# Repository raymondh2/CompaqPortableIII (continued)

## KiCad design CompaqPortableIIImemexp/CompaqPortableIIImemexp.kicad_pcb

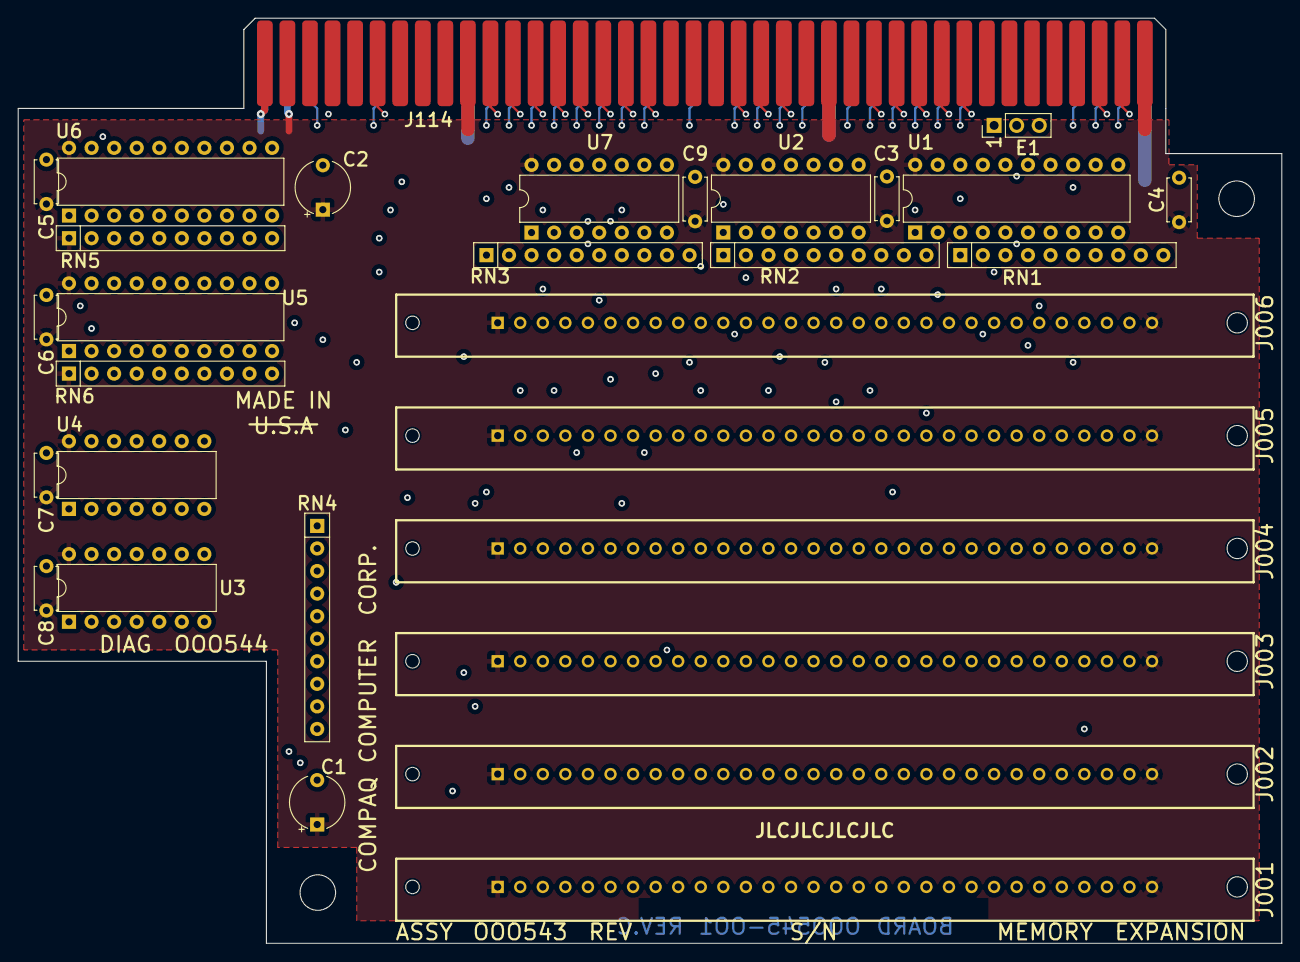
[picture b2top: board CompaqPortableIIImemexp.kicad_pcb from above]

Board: 4 copper layers, 142.2 x 104.1 mm, 32 parts (0 on the bottom side), 104 nets.

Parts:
C1, C2: 10u; CP_Radial_Tantal_D6.0mm_P5.00mm
C3, C4, C5, C6, C7, C8, C9: 47n; C_Disc_D4.7mm_W2.5mm_P5.00mm
E1: Conn_01x03; PinHeader_1x03_P2.54mm_Vertical
H1, H2: MountingHole_Pad; MountingHole_4mm
J001, J002, J003, J004, J005, J006: Conn_SIMM30
J114: Conn_02x40_Counter_Clockwise; Conn_Edge_PCB_02x40_mirror_memexp
RN1, RN2, RN3, RN4: 33; R_Array_SIP10
RN5, RN6: 8.2k; R_Array_SIP10
U1: 74F244; DIP-20_W7.62mm
U2, U4: 74F32; DIP-14_W7.62mm
U3: 74F00; DIP-14_W7.62mm
U5, U6: 74F245; DIP-20_W7.62mm
U7: 74F10; DIP-14_W7.62mm

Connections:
+5V: C1.1, C2.1, C3.1, C4.1, C5.1, C6.1, C7.1, C8.1, C9.1, J001.1 (VCC), J001.30 (VCC), J002.1 (VCC), J002.30 (VCC), J003.1 (VCC), J003.30 (VCC), J004.1 (VCC), J004.30 (VCC), J005.1 (VCC), J005.30 (VCC), J006.1 (VCC), J006.30 (VCC), J114.39, J114.41, J114.55, J114.71, RN5.1 (common), RN6.1 (common), U1.20 (VCC), U2.14 (VCC), U3.14 (VCC), U4.14 (VCC), U5.20 (VCC), U6.20 (VCC), U7.14 (VCC)
/1u3-16j114: J114.16, U3.1
/2u7-58j114: J114.58, U7.2, U7.3, U7.10
/8u4-19u6: U4.8, U6.19 (CE)
/11u4-19u5: U4.11, U5.19 (CE)
/12u4-21j114: J114.21, U4.10, U4.12
/13u3-17j114: J114.17, U3.13
/17u1-2E1: E1.2, U1.15 (I2b)
/A2: E1.3, J114.38
/A10: J114.9, U2.9, U2.12
/CAS: J114.35, U3.2, U3.12
/CASEVEN: J002.2 (~CAS), J002.28 (~CASP), J004.2 (~CAS), J004.28 (~CASP), J006.2 (~CAS), J006.28 (~CASP), RN4.2 (R1.2)
/CASODD: J001.2 (~CAS), J001.28 (~CASP), J003.2 (~CAS), J003.28 (~CASP), J005.2 (~CAS), J005.28 (~CASP), RN4.4 (R2.2)
/MA0: J114.10, U1.17 (I3b)
/MA1: E1.1, J114.50
/MA2: J114.11, U1.13 (I1b)
/MA3: J114.51, U1.11 (I0b)
/MA4: J114.12, U1.8 (I3a)
/MA5: J114.52, U1.6 (I2a)
/MA6: J114.13, U1.4 (I1a)
/MA7: J114.53, U1.2 (I0a)
/MA8: J114.14, U2.1, U2.4
/MEM-A0: J001.4 (A0), J002.4 (A0), J003.4 (A0), J004.4 (A0), J005.4 (A0), J006.4 (A0), RN2.6 (R3.2)
/MEM-A1: J001.5 (A1), J002.5 (A1), J003.5 (A1), J004.5 (A1), J005.5 (A1), J006.5 (A1), RN2.4 (R2.2)
/MEM-A2: J001.7 (A2), J002.7 (A2), J003.7 (A2), J004.7 (A2), J005.7 (A2), J006.7 (A2), RN2.2 (R1.2)
/MEM-A3: J001.8 (A3), J002.8 (A3), J003.8 (A3), J004.8 (A3), J005.8 (A3), J006.8 (A3), RN1.10 (R5.2)
/MEM-A4: J001.11 (A4), J002.11 (A4), J003.11 (A4), J004.11 (A4), J005.11 (A4), J006.11 (A4), RN1.8 (R4.2)
/MEM-A5: J001.12 (A5), J002.12 (A5), J003.12 (A5), J004.12 (A5), J005.12 (A5), J006.12 (A5), RN1.6 (R3.2)
/MEM-A6: J001.14 (A6), J002.14 (A6), J003.14 (A6), J004.14 (A6), J005.14 (A6), J006.14 (A6), RN1.4 (R2.2)
/MEM-A7: J001.15 (A7), J002.15 (A7), J003.15 (A7), J004.15 (A7), J005.15 (A7), J006.15 (A7), RN1.2 (R1.2)
/MEMEVEN-A8: J002.17 (A8), J004.17 (A8), J006.17 (A8), RN2.10 (R5.2)
/MEMEVEN-A9: J002.18 (A9), J004.18 (A9), J006.18 (A9), RN3.4 (R2.2)
/MEMEVEN-DP: J002.29 (DP), J004.29 (DP), J006.29 (DP), J114.42
/MEMEVEN-QP: J002.26 (QP), J004.26 (QP), J006.26 (QP), J114.43
/MEMODD-A8: J001.17 (A8), J003.17 (A8), J005.17 (A8), RN2.8 (R4.2)
/MEMODD-A9: J001.18 (A9), J003.18 (A9), J005.18 (A9), RN3.2 (R1.2)
/MEMODD-DP: J001.29 (DP), J003.29 (DP), J005.29 (DP), J114.2
/MEMODD-QP: J001.26 (QP), J003.26 (QP), J005.26 (QP), J114.3
/MEM_WEDIR: RN3.10 (R5.2), U5.1 (A->B), U6.1 (A->B)
/Memory/MD0: J001.3 (DQ0), J003.3 (DQ0), J005.3 (DQ0), RN6.7 (R6), U5.14 (B4)
/Memory/MD1: J001.6 (DQ1), J003.6 (DQ1), J005.6 (DQ1), RN6.9 (R8), U5.12 (B6)
/Memory/MD2: J001.10 (DQ2), J003.10 (DQ2), J005.10 (DQ2), RN6.8 (R7), U5.13 (B5)
/Memory/MD3: J001.13 (DQ3), J003.13 (DQ3), J005.13 (DQ3), RN6.10 (R9), U5.11 (B7)
/Memory/MD4: J001.16 (DQ4), J003.16 (DQ4), J005.16 (DQ4), RN6.5 (R4), U5.16 (B2)
/Memory/MD5: J001.20 (DQ5), J003.20 (DQ5), J005.20 (DQ5), RN6.4 (R3), U5.17 (B1)
/Memory/MD6: J001.23 (DQ6), J003.23 (DQ6), J005.23 (DQ6), RN6.3 (R2), U5.18 (B0)
/Memory/MD7: J001.25 (DQ7), J003.25 (DQ7), J005.25 (DQ7), RN6.6 (R5), U5.15 (B3)
/Memory/MD8: J002.3 (DQ0), J004.3 (DQ0), J006.3 (DQ0), RN5.7 (R6), U6.14 (B4)
/Memory/MD9: J002.6 (DQ1), J004.6 (DQ1), J006.6 (DQ1), RN5.9 (R8), U6.12 (B6)
/Memory/MD10: J002.10 (DQ2), J004.10 (DQ2), J006.10 (DQ2), RN5.8 (R7), U6.13 (B5)
/Memory/MD11: J002.13 (DQ3), J004.13 (DQ3), J006.13 (DQ3), RN5.6 (R5), U6.15 (B3)
/Memory/MD12: J002.16 (DQ4), J004.16 (DQ4), J006.16 (DQ4), RN5.4 (R3), U6.17 (B1)
/Memory/MD13: J002.20 (DQ5), J004.20 (DQ5), J006.20 (DQ5), RN5.5 (R4), U6.16 (B2)
/Memory/MD14: J002.23 (DQ6), J004.23 (DQ6), J006.23 (DQ6), RN5.10 (R9), U6.11 (B7)
/Memory/MD15: J002.25 (DQ7), J004.25 (DQ7), J006.25 (DQ7), RN5.3 (R2), U6.18 (B0)
/RAM 2 RAS: J114.57, U7.5
/RAM 3 RAS: J114.19, U7.9
/RAM 4 RAS: J114.59, U7.1
/RAS: J114.18, U3.4, U7.4, U7.11, U7.13
/RAS1: J001.27 (~RAS), J002.27 (~RAS), RN4.10 (R5.2)
/RAS2: J003.27 (~RAS), J004.27 (~RAS), RN4.8 (R4.2)
/RAS3: J005.27 (~RAS), J006.27 (~RAS), RN4.6 (R3.2)
/SA0: J114.49, U4.13
/SBHE: J114.75, U4.9
/SD0: J114.23, U5.6 (A4)
/SD1: J114.63, U5.8 (A6)
/SD2: J114.24, U5.7 (A5)
/SD3: J114.64, U5.9 (A7)
/SD4: J114.25, U5.4 (A2)
/SD5: J114.65, U5.3 (A1)
/SD6: J114.26, U5.2 (A0)
/SD7: J114.66, U5.5 (A3)
/SD8: J114.27, U6.6 (A4)
/SD9: J114.67, U6.8 (A6)
/SD10: J114.28, U6.7 (A5)
/SD11: J114.68, U6.5 (A3)
/SD12: J114.29, U6.3 (A1)
/SD13: J114.69, U6.4 (A2)
/SD14: J114.30, U6.9 (A7)
/SD15: J114.70, U6.2 (A0)
/WEEVEN: J002.21 (~WE), J004.21 (~WE), J006.21 (~WE), RN3.6 (R3.2)
/WEODD: J001.21 (~WE), J003.21 (~WE), J005.21 (~WE), RN3.8 (R4.2)
/~MEMW: J114.4, U3.5, U4.2, U4.5
GND: C1.2, C2.2, C3.2, C4.2, C5.2, C6.2, C7.2, C8.2, C9.2, J001.9 (GND), J001.22 (GND), J002.9 (GND), J002.22 (GND), J003.9 (GND), J003.22 (GND), J004.9 (GND), J004.22 (GND), J005.9 (GND), J005.22 (GND), J006.9 (GND), J006.22 (GND), J114.1, J114.15, J114.31, J114.40, J114.80, U1.1 (OEa), U1.10 (GND), U1.19 (OEb), U2.2, U2.5, U2.7 (GND), U2.10, U2.13, U3.7 (GND), U4.1, U4.4, U4.7 (GND), U5.10 (GND), U6.10 (GND), U7.7 (GND)
unnamed: RN1.1 (R1.1), U1.18 (O0a)
unnamed: RN1.3 (R2.1), U1.16 (O1a)
unnamed: RN1.5 (R3.1), U1.14 (O2a)
unnamed: RN1.7 (R4.1), U1.12 (O3a)
unnamed: RN1.9 (R5.1), U1.9 (O0b)
unnamed: RN2.1 (R1.1), U1.7 (O1b)
unnamed: RN2.3 (R2.1), U1.5 (O2b)
unnamed: RN2.5 (R3.1), U1.3 (O3b)
unnamed: RN2.7 (R4.1), U2.3
unnamed: RN2.9 (R5.1), U2.6
unnamed: RN3.1 (R1.1), U2.8
unnamed: RN3.3 (R2.1), U2.11
unnamed: RN3.5 (R3.1), U4.3
unnamed: RN3.7 (R4.1), U4.6
unnamed: RN3.9 (R5.1), U3.6
unnamed: RN4.1 (R1.1), U3.11
unnamed: RN4.3 (R2.1), U3.3
unnamed: RN4.5 (R3.1), U7.12
unnamed: RN4.7 (R4.1), U7.8
unnamed: RN4.9 (R5.1), U7.6

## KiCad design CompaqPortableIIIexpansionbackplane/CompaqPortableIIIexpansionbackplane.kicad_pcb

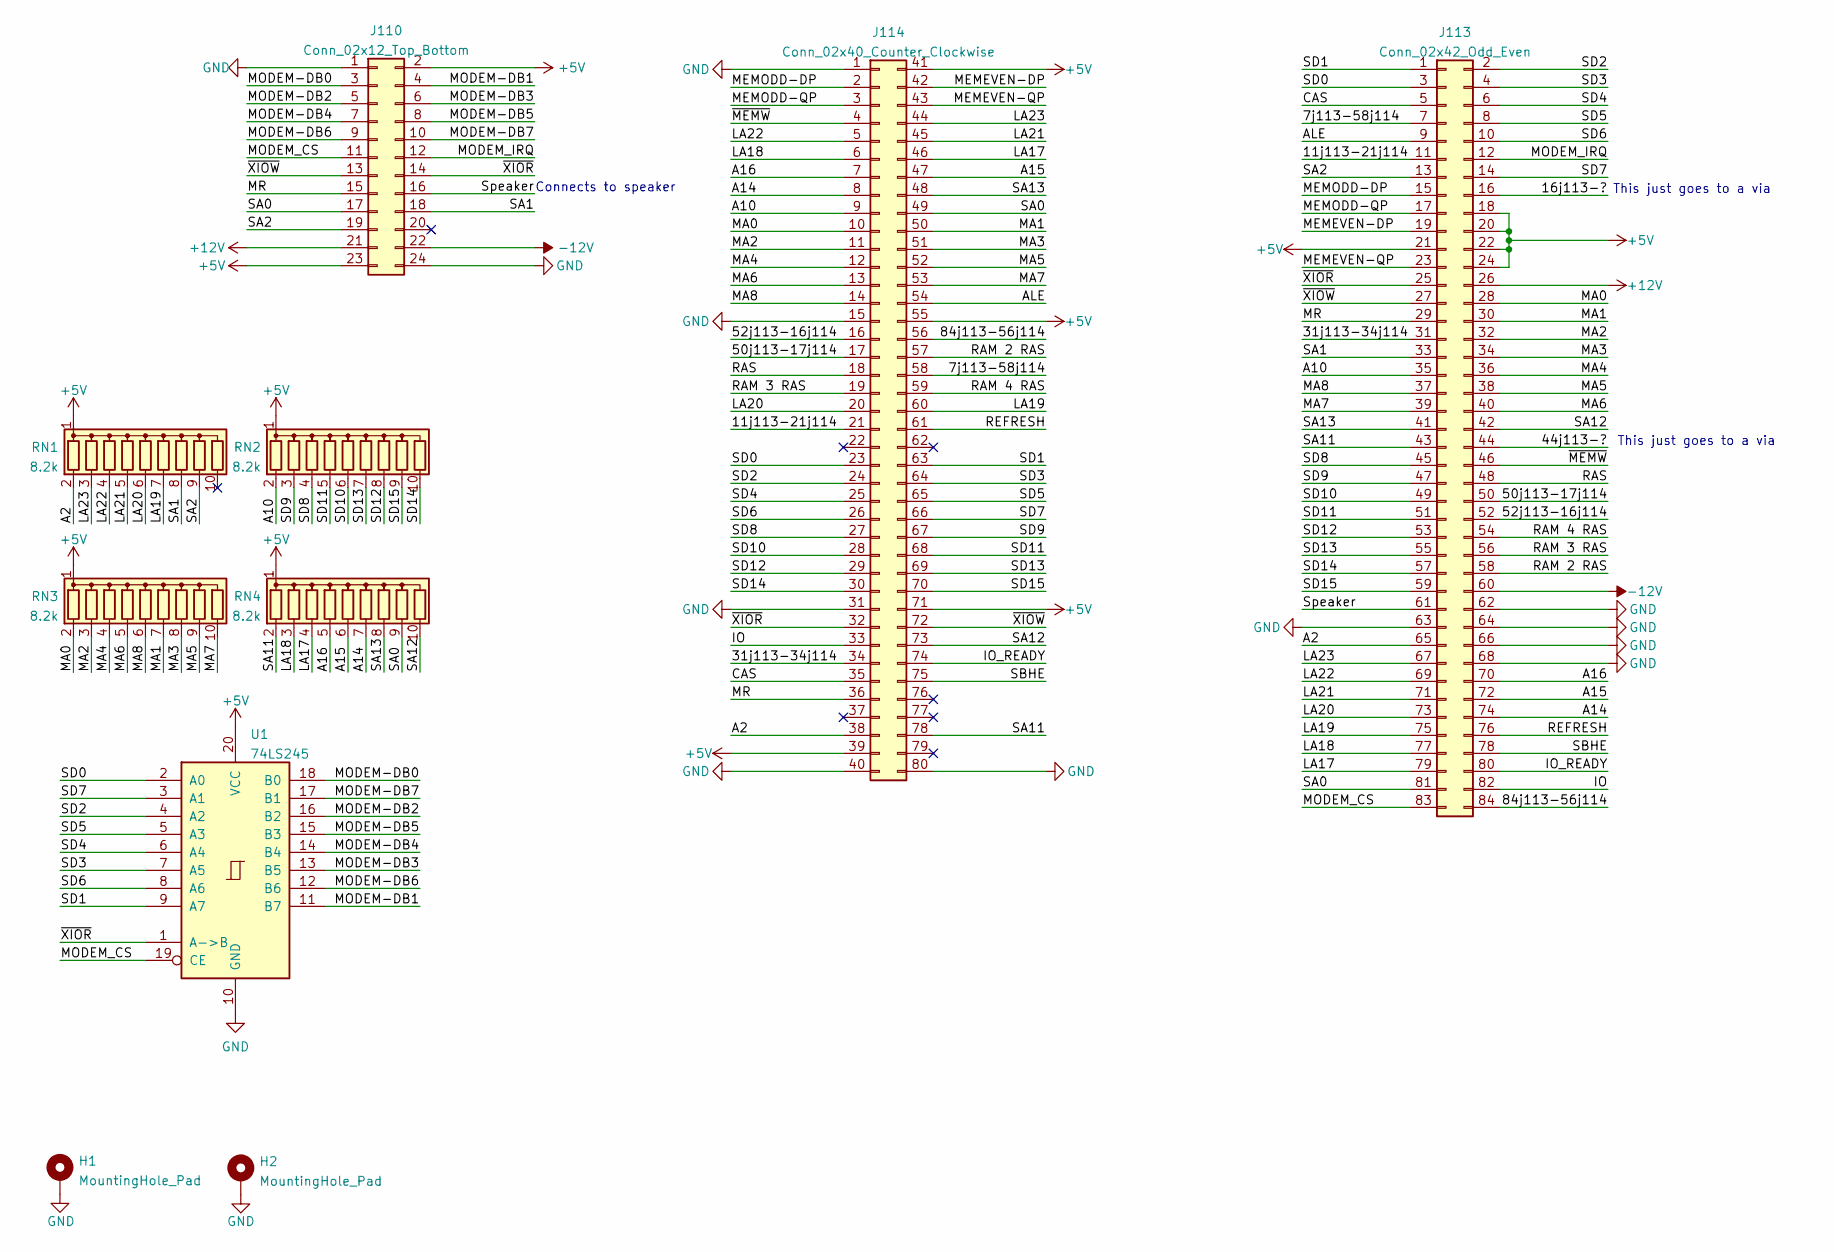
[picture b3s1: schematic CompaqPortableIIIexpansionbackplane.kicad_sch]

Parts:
H1, H2: MountingHole_Pad; MountingHole_4mm_Pad_TopOnly
J110: Conn_02x12_Top_Bottom; 5530843-1_oddeven; PartNumber 5530843-1
J113: Conn_02x42_Odd_Even; PinSocket_2x42_P1.27mm_Vertical_2.54row; PartNumber 6-104068-7
J114: Conn_02x40_Counter_Clockwise; 2-5530843-0_mirror; PartNumber 2-5530843-0
RN1, RN2, RN3, RN4: 8.2k; R_Array_SIP10; PartNumber 4610X-101-822LF
U1: 74LS245; DIP-20_W7.62mm; PartNumber 74LS245N

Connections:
+5V: J110.2, J110.23, J113.18, J113.20, J113.21, J113.22, J113.24, J114.39, J114.41, J114.55, J114.71, RN1.1 (common), RN2.1 (common), RN3.1 (common), RN4.1 (common), U1.20 (VCC)
+12V: J110.21, J113.26
-12V: J110.22, J113.60
/7j113-58j114: J113.7, J114.58
/11j113-21j114: J113.11, J114.21
/16j113-?: J113.16
/31j113-34j114: J113.31, J114.34
/44j113-?: J113.44
/50j113-17j114: J113.50, J114.17
/52j113-16j114: J113.52, J114.16
/54j113-59j114: J113.54, J114.59
/56j113-19j114: J113.56, J114.19
/84j113-56j114: J113.84, J114.56
/A2: J113.65, J114.38, RN1.2 (R1)
/A10: J113.35, J114.9, RN2.2 (R1)
/A14: J113.74, J114.8, RN4.7 (R6)
/A15: J113.72, J114.47, RN4.6 (R5)
/A16: J113.70, J114.7, RN4.5 (R4)
/ALE: J113.9, J114.54
/BA00: J110.17, J113.81, J114.49, RN4.9 (R8)
/BA01: J110.18, J113.33, RN1.8 (R7)
/BA02: J110.19, J113.13, RN1.9 (R8)
/BA11: J113.43, J114.78, RN4.2 (R1)
/BA12: J113.42, J114.73, RN4.10 (R9)
/BA13: J113.41, J114.48, RN4.8 (R7)
/CAS: J113.5, J114.35
/IO: J113.82, J114.33
/IOR: J110.14, J113.25, J114.32, U1.1 (A->B)
/IOW: J110.13, J113.27, J114.72
/IO_READY: J113.80, J114.74
/LA17: J113.79, J114.46, RN4.4 (R3)
/LA18: J113.77, J114.6, RN4.3 (R2)
/LA19: J113.75, J114.60, RN1.7 (R6)
/LA20: J113.73, J114.20, RN1.6 (R5)
/LA21: J113.71, J114.45, RN1.5 (R4)
/LA22: J113.69, J114.5, RN1.4 (R3)
/LA23: J113.67, J114.44, RN1.3 (R2)
/MA0: J113.28, J114.10, RN3.2 (R1)
/MA1: J113.30, J114.50, RN3.7 (R6)
/MA2: J113.32, J114.11, RN3.3 (R2)
/MA3: J113.34, J114.51, RN3.8 (R7)
/MA4: J113.36, J114.12, RN3.4 (R3)
/MA5: J113.38, J114.52, RN3.9 (R8)
/MA6: J113.40, J114.13, RN3.5 (R4)
/MA7: J113.39, J114.53, RN3.10 (R9)
/MA8: J113.37, J114.14, RN3.6 (R5)
/MEMEVEN-DP: J113.19, J114.42
/MEMEVEN-QP: J113.23, J114.43
/MEMODD-DP: J113.15, J114.2
/MEMODD-QP: J113.17, J114.3
/MODEM-DB0: J110.3, U1.18 (B0)
/MODEM-DB1: J110.4, U1.11 (B7)
/MODEM-DB2: J110.5, U1.16 (B2)
/MODEM-DB3: J110.6, U1.13 (B5)
/MODEM-DB4: J110.7, U1.14 (B4)
/MODEM-DB5: J110.8, U1.15 (B3)
/MODEM-DB6: J110.9, U1.12 (B6)
/MODEM-DB7: J110.10, U1.17 (B1)
/MODEM_CS: J110.11, J113.83, U1.19 (CE)
/MODEM_IRQ: J110.12, J113.12
/MR: J110.15, J113.29, J114.36
/RAS: J113.48, J114.18
/REFRESH: J113.76, J114.61
/SBHE: J113.78, J114.75
/SD0: J113.3, J114.23, U1.2 (A0)
/SD1: J113.1, J114.63, U1.9 (A7)
/SD2: J113.2, J114.24, U1.4 (A2)
/SD3: J113.4, J114.64, U1.7 (A5)
/SD4: J113.6, J114.25, U1.6 (A4)
/SD5: J113.8, J114.65, U1.5 (A3)
/SD6: J113.10, J114.26, U1.8 (A6)
/SD7: J113.14, J114.66, U1.3 (A1)
/SD8: J113.45, J114.27, RN2.4 (R3)
/SD9: J113.47, J114.67, RN2.3 (R2)
/SD10: J113.49, J114.28, RN2.6 (R5)
/SD11: J113.51, J114.68, RN2.5 (R4)
/SD12: J113.53, J114.29, RN2.8 (R7)
/SD13: J113.55, J114.69, RN2.7 (R6)
/SD14: J113.57, J114.30, RN2.10 (R9)
/SD15: J113.59, J114.70, RN2.9 (R8)
/Speaker: J110.16, J113.61
/~MEMW: J113.46, J114.4
/~RAS2: J113.58, J114.57
GND: H1.1, H2.1, J110.1, J110.24, J113.62, J113.63, J113.64, J113.66, J113.68, J114.1, J114.15, J114.31, J114.40, J114.80, U1.10 (GND)

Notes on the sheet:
Connects to speaker
This just goes to a via

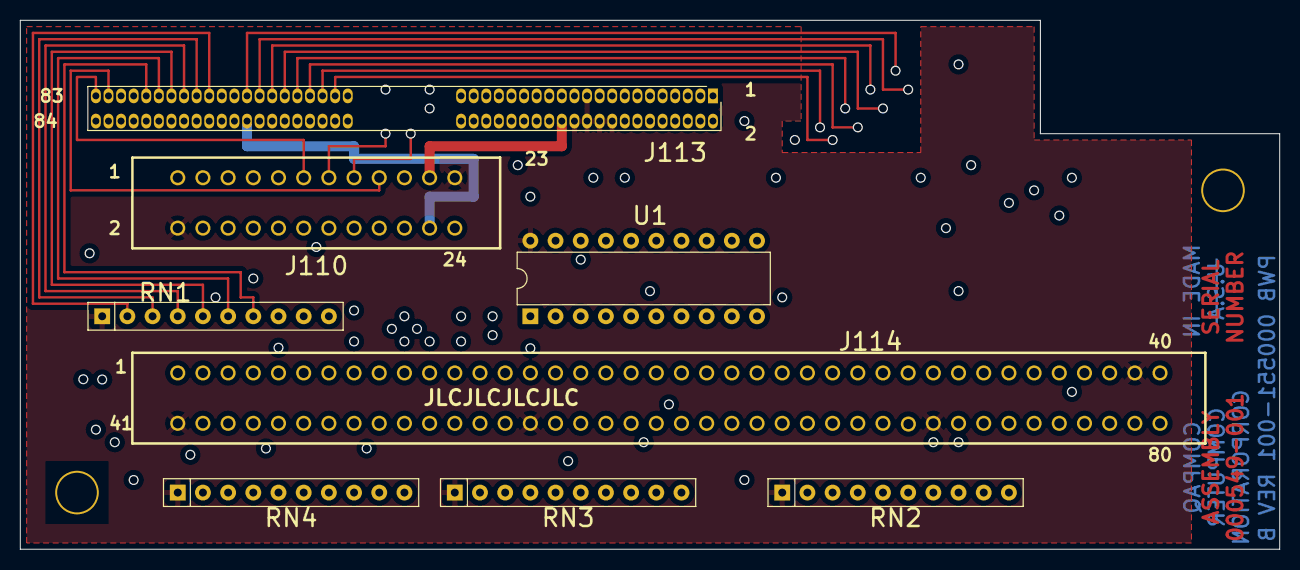
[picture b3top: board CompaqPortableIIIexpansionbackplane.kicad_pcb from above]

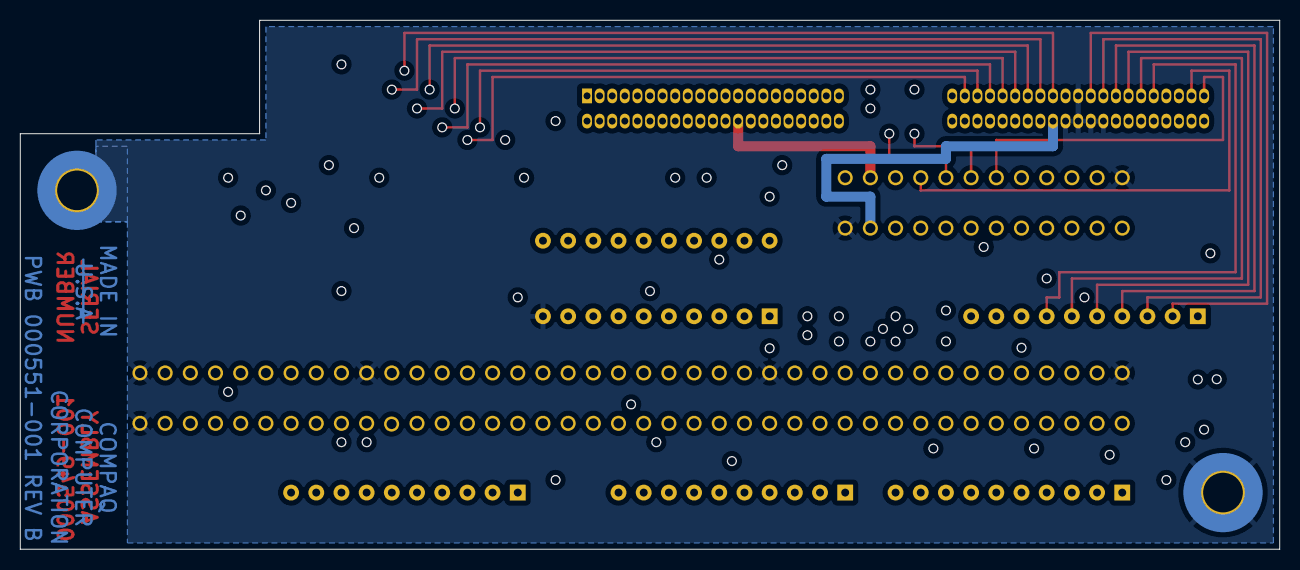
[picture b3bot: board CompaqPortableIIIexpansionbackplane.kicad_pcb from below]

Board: 4 copper layers, 127.0 x 53.3 mm, 10 parts (2 on the bottom side), 82 nets.

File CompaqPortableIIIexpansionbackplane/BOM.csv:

"Reference","Value","PartNumber","Qty"
"J110","Conn_02x12_Top_Bottom","5530843-1","1"
"J113","Conn_02x42_Odd_Even","6-104068-7","1"
"J114","Conn_02x40_Counter_Clockwise","2-5530843-0","1"
"RN1,RN2,RN3,RN4","8.2k","4610X-101-822LF","4"
"U1","74LS245","SN74LS245N","1"

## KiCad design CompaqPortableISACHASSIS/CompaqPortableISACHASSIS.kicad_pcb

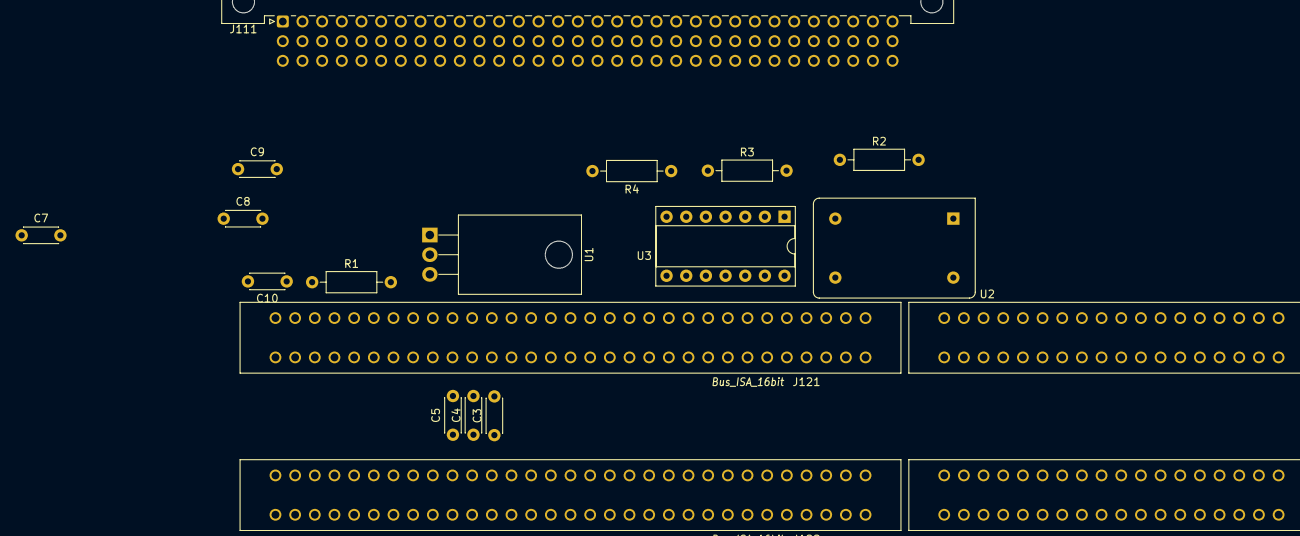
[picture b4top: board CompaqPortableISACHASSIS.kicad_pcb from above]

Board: 2 copper layers, 17 parts (0 on the bottom side), 102 nets, no tracks yet.

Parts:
C3, C7, C10: 10n; C_Disc_D4.3mm_W1.9mm_P5.00mm
C4, C5, C8, C9: 100n; C_Disc_D4.3mm_W1.9mm_P5.00mm
J111: DIN41612_96abc; DIN41612_R_3x32_Male_Horizontal_THT
J121, J122: Bus_ISA_16bit; Conn_Edge_ISA16
R1: 1k; R_Axial_DIN0207_L6.3mm_D2.5mm_P10.16mm_Horizontal
R2, R4: 30?; R_Axial_DIN0207_L6.3mm_D2.5mm_P10.16mm_Horizontal
R3: 150; R_Axial_DIN0207_L6.3mm_D2.5mm_P10.16mm_Horizontal
U1: L7905; TO-220-3_Horizontal_TabDown
U2: CXO_DIP14; Oscillator_DIP-14
U3: 74LS125; DIP-14_W7.62mm_Socket

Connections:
+5V: J121.3 (+5V), J121.29 (VCC), J121.78 (+5V), J122.3 (+5V), J122.29 (VCC), J122.78 (+5V), U2.1 (EN), U2.14 (Vcc), U3.14 (VCC)
+12V: J111.a6 (Pin_c6), J111.a20 (Pin_c20), J121.9 (+12V), J122.9 (+12V)
-5V: J121.5 (-5V), J122.5 (-5V)
-12V: J111.b5 (Pin_c5), J121.7 (-12V), J122.7 (-12V), U1.2 (VI)
/5v_unfused: J111.a2 (Pin_c2), J111.a8 (Pin_c8), J111.c20
/AEN: J111.a7 (Pin_c7), J121.42 (AEN), J122.42 (AEN)
/ALE: J111.b19 (Pin_c19), J121.28 (ALE), J122.28 (ALE)
/BA00: J111.c21, J121.62 (BA00), J122.62 (BA00)
/BA01: J111.b20 (Pin_c20), J121.61 (BA01), J122.61 (BA01)
/BA02: J111.a19 (Pin_c19), J121.60 (BA02), J122.60 (BA02)
/BA03: J111.c19, J121.59 (BA03), J122.59 (BA03)
/BA04: J111.b18 (Pin_c18), J121.58 (BA04), J122.58 (BA04)
/BA05: J111.a17 (Pin_c17), J121.57 (BA05), J122.57 (BA05)
/BA06: J111.c17, J121.56 (BA06), J122.56 (BA06)
/BA07: J111.b16 (Pin_c16), J121.55 (BA07), J122.55 (BA07)
/BA08: J111.a15 (Pin_c15), J121.54 (BA08), J122.54 (BA08)
/BA09: J111.c15, J121.53 (BA09), J122.53 (BA09)
/BA10: J111.b14 (Pin_c14), J121.52 (BA10), J122.52 (BA10)
/BA11: J111.a13 (Pin_c13), J121.51 (BA11), J122.51 (BA11)
/BA12: J111.c13, J121.50 (BA12), J122.50 (BA12)
/BA13: J111.b12 (Pin_c12), J121.49 (BA13), J122.49 (BA13)
/BA14: J111.a11 (Pin_c11), J121.48 (BA14), J122.48 (BA14)
/BA15: J111.c11, J121.47 (BA15), J122.47 (BA15)
/BA16: J111.b10 (Pin_c10), J121.46 (BA16), J122.46 (BA16)
/BA17: J111.a9 (Pin_c9), J121.45 (BA17), J122.45 (BA17)
/BA18: J111.c9, J121.44 (BA18), J122.44 (BA18)
/BA19: J111.b8 (Pin_c8), J121.43 (BA19), J122.43 (BA19)
/CLK: J121.20 (CLK), J122.20 (CLK), R4.2
/D8: J111.b28 (Pin_c28), J121.91 (D8), J122.91 (D8)
/D9: J111.c29, J121.92 (D9), J122.92 (D9)
/D10: J111.a29 (Pin_c29), J121.93 (D10), J122.93 (D10)
/D11: J111.b30 (Pin_c30), J121.94 (D11), J122.94 (D11)
/D12: J111.c31, J121.95 (D12), J122.95 (D12)
/D13: J111.a31 (Pin_c31), J121.96 (D13), J122.96 (D13)
/D14: J111.c32, J121.97 (D14), J122.97 (D14)
/D15: J111.a32 (Pin_c32), J121.98 (D15), J122.98 (D15)
/DB0: J111.b6 (Pin_c6), J121.40 (DB0), J122.40 (DB0)
/DB1: J111.a5 (Pin_c5), J121.39 (DB1), J122.39 (DB1)
/DB2: J111.c5, J121.38 (DB2), J122.38 (DB2)
/DB3: J111.b4 (Pin_c4), J121.37 (DB3), J122.37 (DB3)
/DB4: J111.a3 (Pin_c3), J121.36 (DB4), J122.36 (DB4)
/DB5: J111.c3, J121.35 (DB5), J122.35 (DB5)
/DB6: J111.b2 (Pin_c2), J121.34 (DB6), J122.34 (DB6)
/DB7: J111.a1 (Pin_c1), J121.33 (DB7), J122.33 (DB7)
/DRQ0: J111.b27 (Pin_c27), J121.71 (DRQ0), J122.71 (DRQ0)
/DRQ1: J111.a12 (Pin_c12), J121.18 (DRQ1), J122.18 (DRQ1)
/DRQ2: J111.a4 (Pin_c4), J121.6 (DRQ2), J122.6 (DRQ2)
/DRQ3: J111.b11 (Pin_c11), J121.16 (DRQ3), J122.16 (DRQ3)
/DRQ5: J111.a28 (Pin_c28), J121.73 (DRQ5), J122.73 (DRQ5)
/DRQ6: J111.c30, J121.75 (DRQ6), J122.75 (DRQ6)
/DRQ7: J111.b31 (Pin_c31), J121.77 (DRQ7), J122.77 (DRQ7)
/IO: J111.c1, J121.32 (IO), J122.32 (IO)
/IO_READY: J111.c7, J121.41 (IO_READY), J122.41 (IO_READY)
/IRQ2: J111.b3 (Pin_c3), J121.4 (IRQ2), J122.4 (IRQ2)
/IRQ3: J111.b17 (Pin_c17), J121.25 (IRQ3), J122.25 (IRQ3)
/IRQ4: J111.a16 (Pin_c16), J121.24 (IRQ4), J122.24 (IRQ4)
/IRQ5: J111.c16, J121.23 (IRQ5), J122.23 (IRQ5)
/IRQ6: J111.b15 (Pin_c15), J121.22 (IRQ6), J122.22 (IRQ6)
/IRQ7: J111.a14 (Pin_c14), J121.21 (IRQ7), J122.21 (IRQ7)
/IRQ10: J111.b23 (Pin_c23), J121.65 (IRQ10), J122.65 (IRQ10)
/IRQ11: J111.c24, J121.66 (IRQ11), J122.66 (IRQ11)
/IRQ12: J111.a24 (Pin_c24), J121.67 (IRQ12), J122.67 (IRQ12)
/IRQ14: J111.c26, J121.69 (IRQ14), J122.69 (IRQ14)
/IRQ15: J111.b25 (Pin_c25), J121.68 (IRQ15), J122.68 (IRQ15)
/LA17: J111.b26 (Pin_c26), J121.88 (LA17), J122.88 (LA17)
/LA18: J111.a25 (Pin_c25), J121.87 (LA18), J122.87 (LA18)
/LA19: J111.c25, J121.86 (LA19), J122.86 (LA19)
/LA20: J111.b24 (Pin_c24), J121.85 (LA20), J122.85 (LA20)
/LA21: J111.a23 (Pin_c23), J121.84 (LA21), J122.84 (LA21)
/LA22: J111.c23, J121.83 (LA22), J122.83 (LA22)
/LA23: J111.b22 (Pin_c22), J121.82 (LA23), J122.82 (LA23)
/MASTER: J111.b32 (Pin_c32), J121.79 (MASTER), J122.79 (MASTER)
/OSC: J121.30 (OSC), J122.30 (OSC), R2.2
/OWS_N: J111.c6, J121.8 (UNUSED), J122.8 (UNUSED)
/RESET: C10.1, J111.c2, J121.2 (RESET), J122.2 (RESET)
/SBHE: J111.a21 (Pin_c21), J121.81 (SBHE), J122.81 (SBHE)
/SYSCLK: J111.c14, U3.9
/TC: J111.a18 (Pin_c18), J121.27 (TC), J122.27 (TC)
/~DACK0: J111.a26 (Pin_c26), J121.70 (~DACK0), J122.70 (~DACK0)
/~DACK1: J111.c12, J121.17 (~DACK1), J122.17 (~DACK1)
/~DACK2: J111.c18, J121.26 (~DACK2), J122.26 (~DACK2)
/~DACK3: J111.a10 (Pin_c10), J121.15 (~DACK3), J122.15 (~DACK3)
/~DACK5: J111.c28, J121.72 (~DACK5), J122.72 (~DACK5)
/~DACK6: J111.b29 (Pin_c29), J121.74 (~DACK6), J122.74 (~DACK6)
/~DACK7: J111.a30 (Pin_c30), J121.76 (~DACK7), J122.76 (~DACK7)
/~FIRSTMB: J111.c8, U3.1, U3.4
/~IOCS16: J111.a22 (Pin_c22), J121.64 (~IOCS16), J122.64 (~IOCS16)
/~IOR: J111.c10, J121.14 (~IOR), J122.14 (~IOR)
/~IOW: J111.b9 (Pin_c9), J121.13 (~IOW), J122.13 (~IOW)
/~MEMCS16: J111.c22, J121.63 (~MEMCS16), J122.63 (~MEMCS16)
/~MEMR: J111.c27, J121.89 (~MEMR), J122.89 (~MEMR), U3.5
/~MEMW: J111.a27 (Pin_c27), J121.90 (~MEMW), J122.90 (~MEMW), U3.2
/~REFRESH: J111.b13 (Pin_c13), J121.19 (~REFRESH), J122.19 (~REFRESH)
/~SMEMR: J121.12 (~SMEMR), J122.12 (~SMEMR), U3.6
/~SMEMW: J121.11 (~SMEMW), J122.11 (~SMEMW), U3.3
GND: C3.2, C4.2, C5.2, C7.2, C8.2, C9.2, C10.2, J111.b1 (Pin_c1), J111.b7 (Pin_c7), J111.b21 (Pin_c21), J111.c4, J121.1 (GND), J121.10 (GND), J121.31 (GND), J121.80 (GND), J122.1 (GND), J122.10 (GND), J122.31 (GND), J122.80 (GND), R1.1, R3.1, U1.1 (GND), U2.7 (GND), U3.7 (GND), U3.10
unnamed: R1.2, U1.3 (VO)
unnamed: C3.1, C4.1, C5.1, C7.1, C8.1, C9.1
unnamed: R2.1, U3.8
unnamed: R3.2, U3.13
unnamed: R4.1, U3.11
unnamed: U2.8 (OUT), U3.12

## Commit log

2022-08-03 Update readme with CC license
2022-08-03 Add ISA card schematic
2022-08-24 Change License
2022-08-24 Actually Change License
2022-08-24 Add memory and modem backplane card schematic, and memory expansion card
2022-08-24 Add related projects
2022-10-12 Add Memory PCB
2022-10-12 Add backplan PCB
2022-10-12 Mention untested state
2022-10-12 Add license notice
2022-10-12 Remove space
2022-11-17 Add Compaq Portable III U10 PAL Code (tested)
2022-11-17 Add Compaq Portable III U20 PAL Code (untested)
2024-05-04 Update netnames based on further research
2024-05-04 Add CSV BOM
2024-05-04 Update BOMs
2024-05-04 Allow CSV files
2024-05-04 Add reverse engineered schematic of mainboard
